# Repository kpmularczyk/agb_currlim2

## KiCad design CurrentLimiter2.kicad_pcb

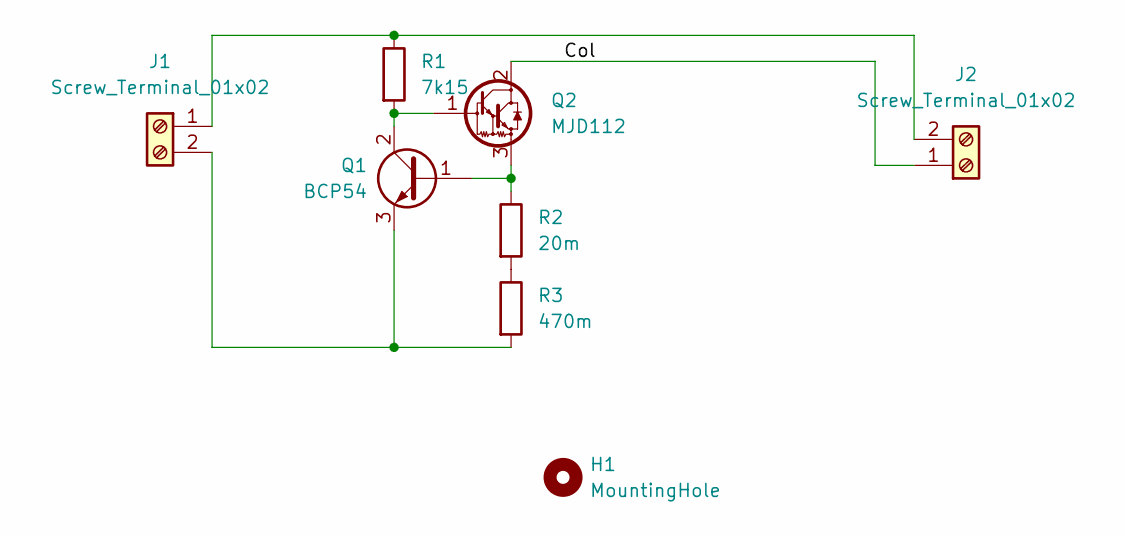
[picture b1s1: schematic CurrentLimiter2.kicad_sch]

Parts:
H1: MountingHole; MountingHole_3.2mm_M3
J1, J2: Screw_Terminal_01x02; TerminalBlock_RND_205-00067_1x02_P7.50mm_Horizontal
Q1: BCP54; SOT-223-3_TabPin2
Q2: MJD112; TO-252-2
R1: 7k15; R_0805_2012Metric_Pad1.20x1.40mm_HandSolder
R2: 20m; R_1206_3216Metric_Pad1.30x1.75mm_HandSolder
R3: 470m; R_2010_5025Metric_Pad1.40x2.65mm_HandSolder

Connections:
/Col: J2.1, Q2.2 (C)
unnamed: J1.1, J2.2, R1.1
unnamed: J1.2, Q1.3 (B), R3.2
unnamed: Q1.2 (C), Q2.1 (B), R1.2
unnamed: Q1.1 (E), Q2.3 (E), R2.1
unnamed: R2.2, R3.1

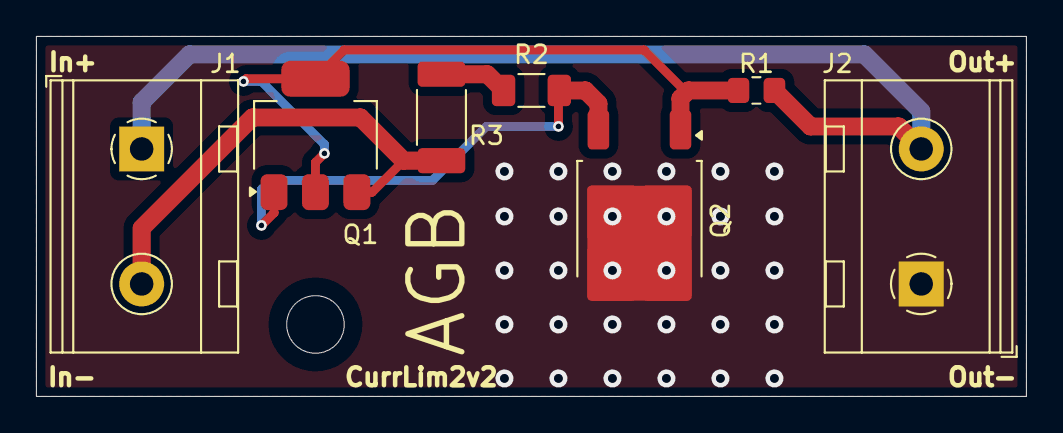
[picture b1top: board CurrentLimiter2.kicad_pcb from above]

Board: 2 copper layers, 55.0 x 20.0 mm, 8 parts (0 on the bottom side), 6 nets.

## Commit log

2024-08-23 komit poczatkowy, seria probna, blad w footprincie npn bjt- zamianiona b z e
2024-08-23 v2 wersja wyslana do Elpinu do wykonania i zmontowania w Blaberk
2024-08-23 zmieniona podstawka Darlingtona na 2 pinowa
